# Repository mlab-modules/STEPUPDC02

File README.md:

<!--- PrjInfo ---> <!--- Please remove this line after manually editing --->
<!--- 00a56be08b96043df9e37d6aff7b6990 --->
<!--- Created:2019-04-08 14:18:05.740877: --->
<!--- Author:: --->
<!--- AuthorEmail:: --->
<!--- Tags:: --->
<!--- Ust:: --->
<!--- Label --->
<!--- ELabel --->
<!--- Name:STEPUPDC02A: --->
# STEPUPDC02A
<!--- LongName --->
##
<!--- ELongName --->

<!--- Lead --->

<!--- ELead --->

<!--- Description --->
<!--- EDescription --->
<!--- Content --->
<!--- EContent --->
<sub><sup> Generated with [MLABweb](https://github.com/MLAB-project/MLABweb). (2019-04-08)</sup></sub>

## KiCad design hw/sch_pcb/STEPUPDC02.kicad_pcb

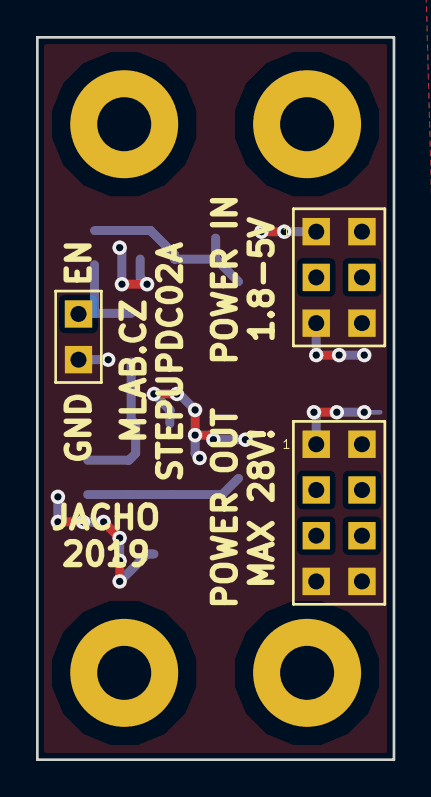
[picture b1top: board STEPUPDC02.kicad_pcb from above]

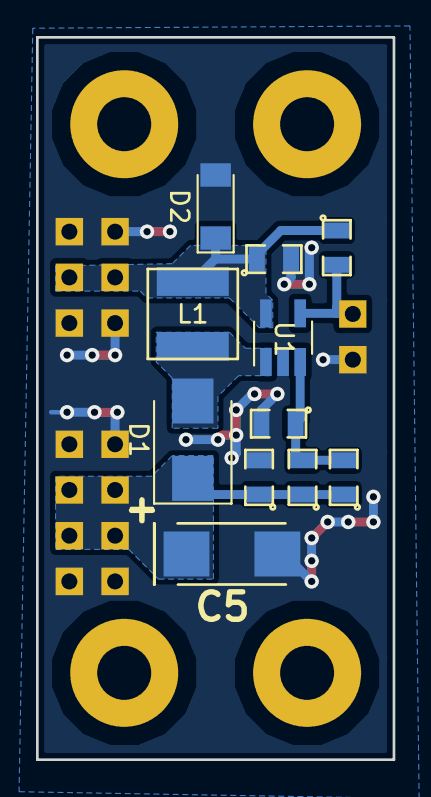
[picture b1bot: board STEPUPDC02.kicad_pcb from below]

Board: 2 copper layers, 19.8 x 40.1 mm, 18 parts (11 on the bottom side), 6 nets.

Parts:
C1: 22p; SMD-0805
C2: 1uF/50V; SMD-0805
C5: 15uF/35V; TantalC_SizeC_Reflow
C6: 4u7; SMD-0805
D1: STPS1L30U; D_SMB
D2: ZSMD-5V6; D_MiniMELF
J1: POWER; Straight_2x03
J2: HEADER_1x02; Straight_2x01
J4: HEADER_2x04_PARALLEL; Straight_2x04
L1: 10u; DJNR5040
M1, M2, M3, M4: HOLE; MountingHole_3mm
R1: 10k; SMD-0805
R2: 470k; SMD-0805
R4: 120k; SMD-0805
U1: TPS6104; SOT-23-5_HandSoldering

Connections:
/ENABLE: J2.2, R1.2, U1.4
/Power: C6.1, D2.1, J1.3, J1.4, L1.1, R1.1, U1.5
/PowerOUT: C1.1, C2.1, C5.1, D1.1, J4.3, J4.4, J4.5, J4.6, R2.1
GND: C2.2, C5.2, C6.2, D2.2, J1.1, J1.2, J1.5, J1.6, J2.1, J4.1, J4.2, J4.7, J4.8, R4.2, U1.2
unnamed: C1.2, R2.2, R4.1, U1.3
unnamed: D1.2, L1.2, U1.1

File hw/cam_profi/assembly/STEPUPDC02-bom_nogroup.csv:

Component,Description,Part,References,Value,Footprint,Quantity Per PCB,Datasheet,ust_id
1,,C,C1,22p,SMD-0805,1,,5c70984712875079b91f8b34
2,,C,C6,4u7,SMD-0805,1,,5c70984712875079b91f8b52
3,,CP,C5,15uF/35V,TantalC_SizeC_Reflow,1,,5c70984812875079b91f8bac
4,,C,C2,1uF/50V,SMD-0805,1,,5c70984712875079b91f8b6f
5,,D_Schottky,D1,STPS340U,D_SMB,1,,5c70984512875079b91f88ba
6,,D_Zener,D2,ZSMD-5V6,D_MiniMELF,1,,5c70984512875079b91f88bc
7,,HEADER_1x02,J2,HEADER_1x02,Straight_2x01,1,,
8,,HEADER_2x04_PARALLEL,J4,HEADER_2x04_PARALLEL,Straight_2x04,1,,
9,,HEADER_2x03_PARALLEL,J1,POWER,Straight_2x03,1,,
10,,L,L1,10u-DJNR5040-100-S,DJNR5040,1,,5c70984412875079b91f882a
11,,R,R1,10k,SMD-0805,1,,5c70984612875079b91f899f
12,,R,R4,80k6,SMD-0805,1,,5cb467d31287500e61c242d2
13,,R,R2,1M8,SMD-0805,1,,5c70984712875079b91f8aab
14,,TPS6104,U1,TPS61041,SOT-23-5_HandSoldering,1,,5c70984612875079b91f8a0e

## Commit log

2019-01-08 [MLABweb] Documentaion edits; STEPUPDC02A
2019-04-08 Nový modul
2019-04-15 Edit
2021-12-25 Improve the documentation. a
2022-04-06 automated commit; add github actions
2022-04-06 Update actions products
2023-05-25 Update metadata files
2023-05-28 Update workflow files
2023-07-05 automated commit; rename source files to new naming convence
2023-09-16 Update image to image_title
2023-09-16 Update status
